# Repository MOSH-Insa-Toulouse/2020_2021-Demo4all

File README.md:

# 2020_2021-Demo4all

My Project Shield Arduino

Contact : [ArnauldDev](biganzol@insa-toulouse.fr)

- [x] Ajouter de nouveaux fichiers
- [x] Les ajouter à l'index de suivi
- [x] Faire un commit (en local sur mon PC)
- [x] Pousser le ou les commit vers le serveur
- [x] Créer une nouvelle branche
- [x] Basculer sur cette branche

---

## 2020_2021-Demo4all

### Arduino Project

ArduinoSerialEventDemo

```C++
// print the string when a newline arrives:
if (stringComplete)
{
    Serial.println(); // faire un saut de ligne entre les réponses
    Serial.print("Vous avez repondu ");
    Serial.println(inputString);
    // test de la réponse du joueur
    if (inputString == "kicad")
    {
        Serial.println("Go for a new PCB board!");
    }
    else
    {
        Serial.println("C'est pas tout a fait ca...");
    }
    // clear the string:
    inputString = "";
    stringComplete = false;
}
```

### KiCad - Shield for Arduino

#### TODO Concevoir une carte avec KiCad

- [x] Créer un projet de PCB pour réaliser une shield Arduino
- [x] Saisi du schéma
- [x] Vérification des tests électriques **ERC**
- [x] Association des empreintes de composants avec leur boitier
- [x] Génération de la netlist
- [x] Conception de la carte électronique
- [x] Importation de la netlist
- [x] Placement des composants
- [x] Définir les contraintes de conception de la carte électronique ([stackup](https://www.emsproto.com/fr/standard-multi-layer-pcb-stackup))
- [x] Router les pistes de la carte électronique

#### KiCad Tools used

[KiCad EDA - Schematic Capture & PCB Design Software](https://kicad.org/), version: 5.1.8

Open source EDA / electronics CAD software for Windows, macOS and Linux.

#### Librairies de composants

* LED_THT:LED_D5.0mm
* Resistor_THT:R_Axial_DIN0207_L6.3mm_D2.5mm_P10.16mm_Horizontal

#### Electrical diagram

## Component placement

<!--  -->

## Routage

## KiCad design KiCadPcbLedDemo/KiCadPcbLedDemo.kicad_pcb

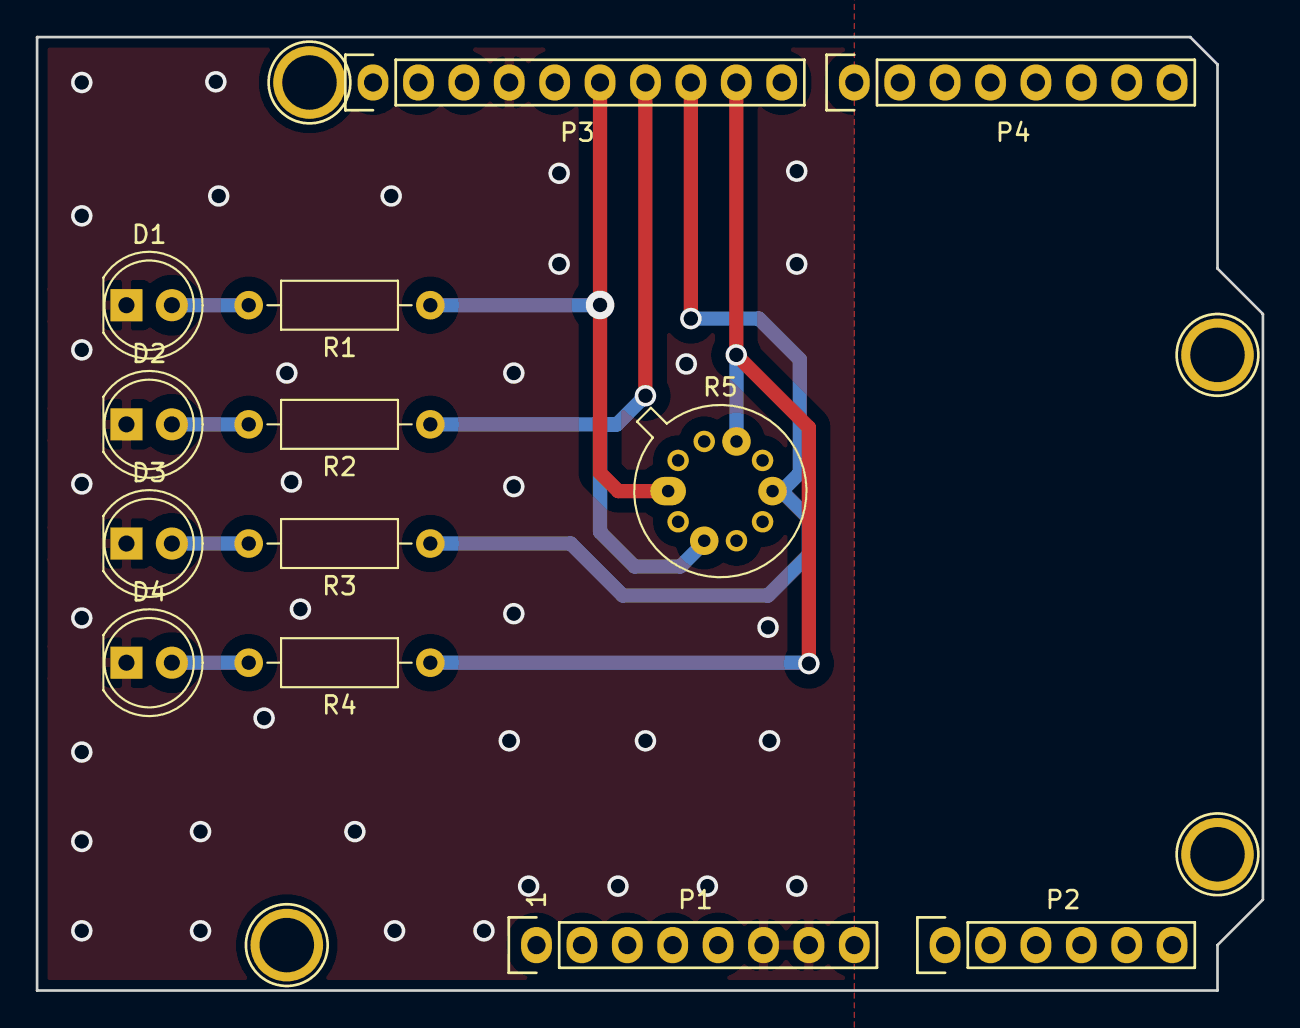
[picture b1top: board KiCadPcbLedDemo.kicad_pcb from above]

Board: 2 copper layers, 68.6 x 53.3 mm, 17 parts (0 on the bottom side), 9 nets.

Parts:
D1, D2, D3, D4: LED; LED_D5.0mm
P1: Power; Socket_Strip_Arduino_1x08
P2: Analog; Socket_Strip_Arduino_1x06
P3: Digital; Socket_Strip_Arduino_1x10
P4: Digital; Socket_Strip_Arduino_1x08
P5, P6, P7, P8: CONN_01X01; Arduino_1pin
R1, R2, R3, R4: 470; R_Axial_DIN0207_L6.3mm_D2.5mm_P10.16mm_Horizontal
R5: GSensor; TO-5-10_Window

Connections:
/LED1: P3.6, R1.1, R5.1
/LED2: P3.7, R2.1, R5.2
/LED3: P3.8, R3.1, R5.3
/LED4: P3.9, R4.1, R5.4
GND: D1.1, D2.1, D3.1, D4.1, P1.6, P1.7, P3.4
unnamed: D1.2, R1.2
unnamed: D2.2, R2.2
unnamed: D3.2, R3.2
unnamed: D4.2, R4.2

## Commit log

2020-11-20 Add contact
2020-11-20 Add checkbox todo
2020-11-20 New tasks complit
2020-11-20 Add modif on local
2020-11-20 Task 3 done
2020-12-02 Solution
2020-12-02 Toto KiCad
2020-12-02 Creation of new pcb project
2020-12-02 Ajout des Net des LED
2020-12-02 ERC check Ok
2020-12-02 Association des empreintes de composants avec leur boitier
2020-12-02 Ajout d'une image pour notre schema
2020-12-02 Placement des componants
2020-12-02 Definir les contraintes de conception de la carte electronique
2020-12-04 Add 3D view
2020-12-07 Creation du symbole du capteur de gaz
2020-12-07 Routage de la carte avec le capteur de gaz
2020-12-07 Ajout d'un tableau pour la mise en forme des images
2021-11-10 Update README.md
    https://forum.kicad.info/t/warning-avoid-all-links-to-kicad-pcb-org-use-kicad-org/31521
